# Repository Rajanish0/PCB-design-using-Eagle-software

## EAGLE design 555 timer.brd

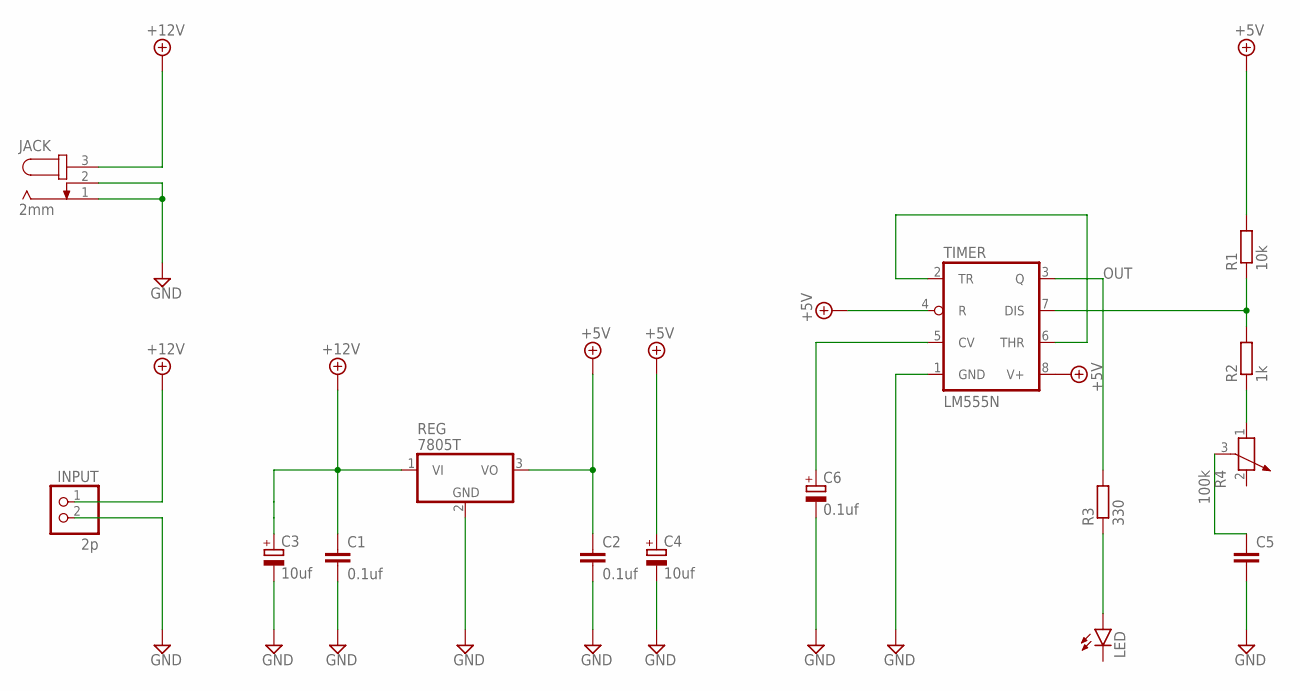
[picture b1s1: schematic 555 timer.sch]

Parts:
C1, C2: 0.1uf; C025-030X050
C3, C4: 10uf; E2,5-6E
C5: C-EU025-030X050; C025-030X050
C6: 0.1uf; E2,5-6E
INPUT: 2p; 1X02
JACK: 2mm; SPC4077
LED: LED5MM
R1: 10k; 0411/15
R2: 1k; 0411/15
R3: 330; 0411/15
R4: 100k; PT-10S
REG: 7805T; TO220H
TIMER: LM555N; DIL08

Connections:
+5V: C2.1, C4.+, R1.2, REG.3 (VO), TIMER.4 (R), TIMER.8 (V+)
+12V: C1.1, C3.+, INPUT.1, JACK.3, REG.1 (VI)
GND: C1.2, C2.2, C3.-, C4.-, C5.2, C6.-, JACK.1, JACK.2, REG.2 (GND), TIMER.1 (GND)
INPUT: INPUT.2
unnamed: C6.+, TIMER.5 (CV)
unnamed: R1.1, R2.2, TIMER.7 (DIS)
unnamed: R2.1, R4.1
unnamed: C5.1, R4.3
unnamed: LED.A, R3.1
OUT: R3.2, TIMER.3 (Q)
TH: TIMER.2 (TR), TIMER.6 (THR)

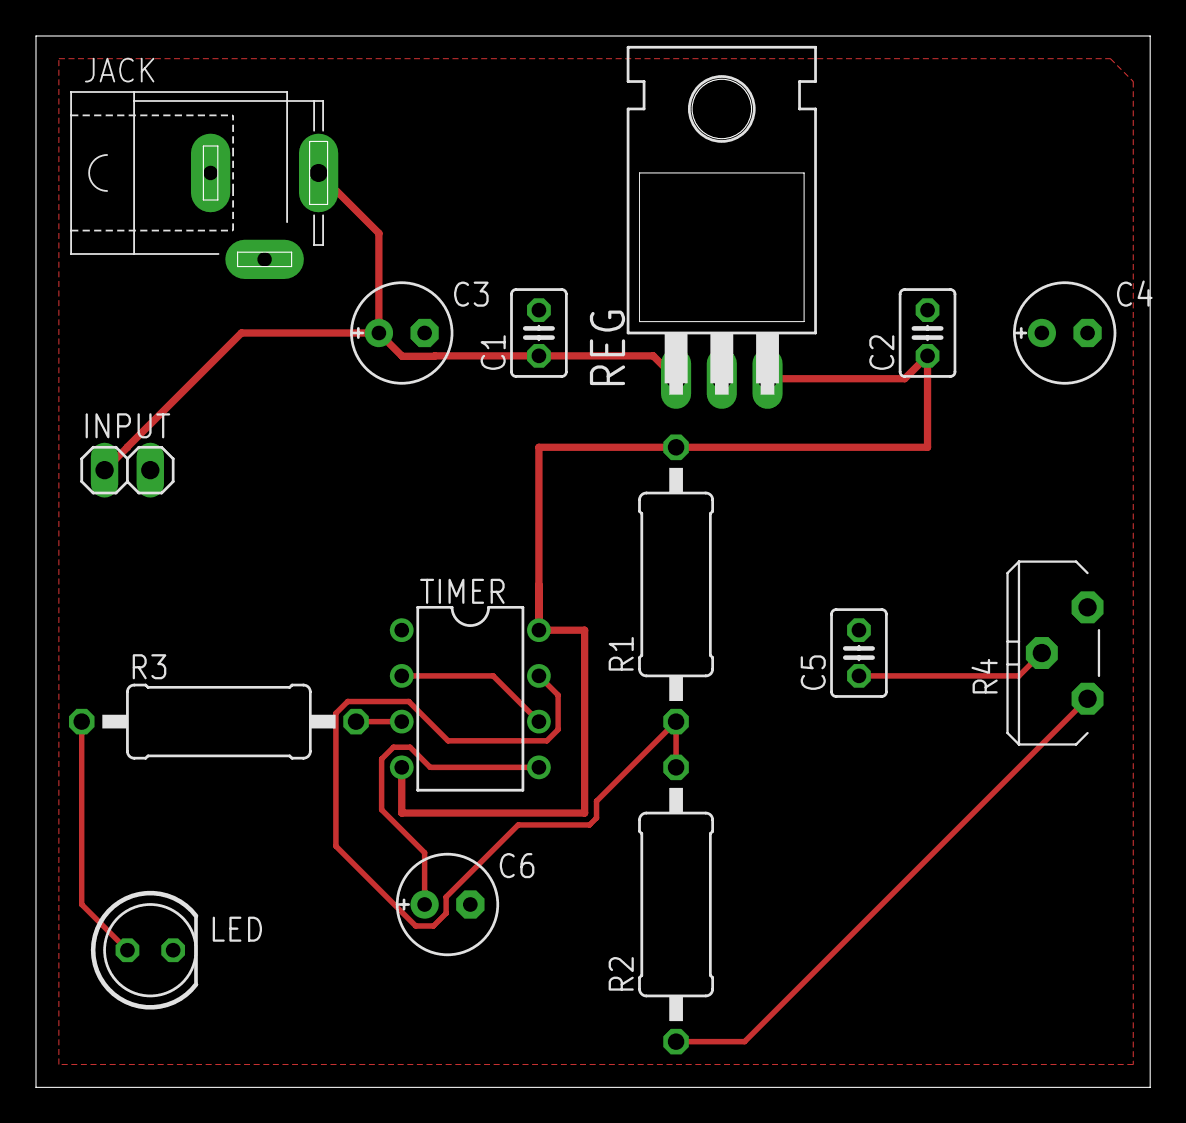
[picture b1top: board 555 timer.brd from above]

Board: 2 copper layers, 61.9 x 58.4 mm, 15 parts (0 on the bottom side), 10 nets.
